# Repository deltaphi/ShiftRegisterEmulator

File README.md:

# ShiftRegisterEmulator
An emulator for a 16-bit shift register. The behavior of this Sketch mimicks
the behavior of an S88 module (i.e., a chain of two 4014B Chips).
The Sketch is set up so that the Arduinos can be Daisy-Chained.

## Hardware Notes

The sketch does not use serial (almost all IO pins are needed). It is set up
not to use the Oscillator Pins. The Sketch can thus be used both with an
external oscillator (e.g., Arduino Board) or without (e.g., Breadboard Setup).

Attempts have been made for a minimal parts setup, where the internal pullup
resistors are used. Thus, you would need only the Atmega and a pull-up resistor
for the reset pin. Unfortunately, I have had repeated trouble with the internal
pull-ups not working as expected (e.g., pulling *down* instead or being an
apparent short), so the default setup is to use external pullups.

In a 3.3V setting, the sketch works when you wire the Atmega up as follows:
* XTAL pins are left open
* All other pins are pulled high using 10k or 47k. Note that the DATA_OUT pin
  does not actually need a pull-up, but having one doesn't hurt functionality.

Note that you can conveniently use star-shaped resistor networks to pull all
pins high with only a few parts.

Note that I have not calculated the input current requirements on the shift
register pins. I use a 74HC367 current driver wired to an ESP32 to drive
the shift register.

### S88 Notes

Here is a not if you want to use this sketch to simulate an S88 module for your
model railroad. This sketch implements the latches of the 4044B chips on an S88
module in software. Therefore, it uses fewer lines. In S88 there are two lines
used for loading the register: "LOAD"/"PS" and "RESET". This sketch only uses
the "LOAD"/"PS" line.

At least on a 16 MHz Arduino, this sketch worked with the most agressive S88
timing I could find (~50us clock). Tests on an 8 MHz Arduino have not been
perfomed yet.

## Software Notes

This sketch was written with [PlatformIO](https://platformio.org/) using the
Arduino framework. It should easily be possible to build and upload it using
the Arduino IDE. You need to rename [src/main.cpp] to something with a
```.ino``` file extension and install the digitalWriteFast library in your
Arduino IDE (not available through the library manager, sadly).

## Why emulate a shift register?

This project started because I needed a bunch of shift register inputs and had
lots of Atmega168 but no 4041B lying around.

## Upcoming Features

* Correct reception of 16 input bits
* Debouncing of input pins over multiple reset-cycles
* Figure out whether using the internal pullups is a good idea (might overload
  the Atmegas' current capacity).

# Dependencies

This sketch uses the digitalWriteFast library (see git submodules).

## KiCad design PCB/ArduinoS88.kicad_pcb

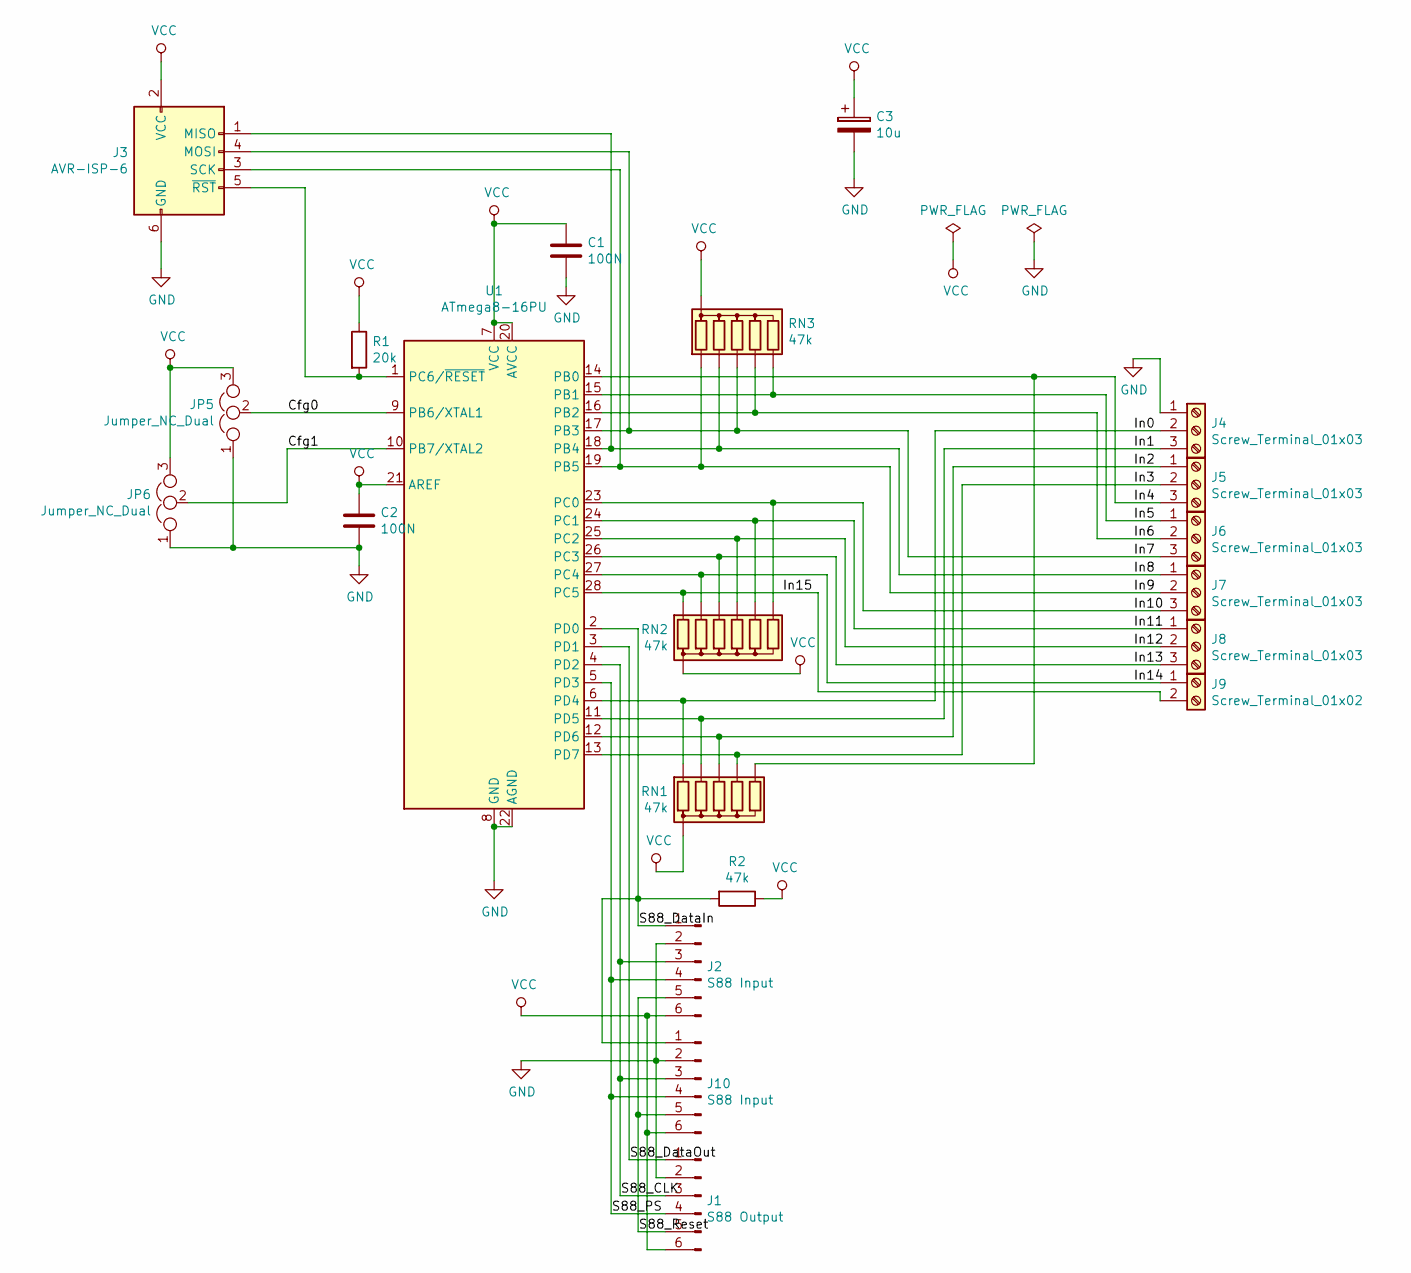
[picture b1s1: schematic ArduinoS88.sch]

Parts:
C1, C2: 100N; C_Disc_D3.0mm_W1.6mm_P2.50mm
C3: 10u; CP_Radial_D4.0mm_P1.50mm
J1: S88 Output; PinHeader_1x06_P2.54mm_Horizontal
J2: S88 Input; PinSocket_1x06_P2.54mm_Horizontal
J3: AVR-ISP-6; IDC-Header_2x03_P2.54mm_Vertical
J4, J5, J6, J7, J8: Screw_Terminal_01x03; TerminalBlock_bornier-3_P5.08mm
J9: Screw_Terminal_01x02; TerminalBlock_bornier-2_P5.08mm
J10: S88 Input; Molex_KK-254_AE-6410-06A_1x06_P2.54mm_Vertical
JP5, JP6: Jumper_NC_Dual; PinHeader_1x03_P2.54mm_Vertical
R1: 20k; R_Axial_DIN0207_L6.3mm_D2.5mm_P10.16mm_Horizontal
R2: 47k; R_Axial_DIN0207_L6.3mm_D2.5mm_P10.16mm_Horizontal
RN1, RN3: 47k; R_Array_SIP6
RN2: 47k; R_Array_SIP7
U1: ATmega8-16PU; DIP-28_W7.62mm

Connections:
/Cfg0: JP5.2, U1.9 (PB6/XTAL1)
/Cfg1: JP6.2, U1.10 (PB7/XTAL2)
/In0: J4.2, RN1.2 (R1), U1.6 (PD4)
/In1: J4.3, RN1.3 (R2), U1.11 (PD5)
/In2: J5.1, RN1.4 (R3), U1.12 (PD6)
/In3: J5.2, RN1.5 (R4), U1.13 (PD7)
/In4: J5.3, RN1.6 (R5), U1.14 (PB0)
/In5: J6.1, RN3.6 (R5), U1.15 (PB1)
/In6: J6.2, RN3.5 (R4), U1.16 (PB2)
/In7: J3.4 (MOSI), J6.3, RN3.4 (R3), U1.17 (PB3)
/In8: J3.1 (MISO), J7.1, RN3.3 (R2), U1.18 (PB4)
/In9: J3.3 (SCK), J7.2, RN3.2 (R1), U1.19 (PB5)
/In10: J7.3, RN2.7 (R6), U1.23 (PC0)
/In11: J8.1, RN2.6 (R5), U1.24 (PC1)
/In12: J8.2, RN2.5 (R4), U1.25 (PC2)
/In13: J8.3, RN2.4 (R3), U1.26 (PC3)
/In14: J9.1, RN2.3 (R2), U1.27 (PC4)
/In15: J9.2, RN2.2 (R1), U1.28 (PC5)
/S88_CLK: J1.3, J2.3, J10.3, U1.4 (PD2)
/S88_DataIn: J2.1, J10.1, R2.2, U1.2 (PD0)
/S88_DataOut: J1.1, U1.3 (PD1)
/S88_PS: J1.4, J2.4, J10.4, U1.5 (PD3)
/S88_Reset: J1.5, J2.5, J10.5
GND: C1.2, C2.2, C3.2, J1.2, J2.2, J3.6 (GND), J4.1, J10.2, JP5.1, JP6.1, U1.8 (GND), U1.22 (AGND)
unnamed: J3.5 (~RST), R1.2, U1.1 (PC6/~RESET)
VCC: C1.1, C2.1, C3.1, J1.6, J2.6, J3.2 (VCC), J10.6, JP5.3, JP6.3, R1.1, R2.1, RN1.1 (common), RN2.1 (common), RN3.1 (common), U1.7 (VCC), U1.20 (AVCC), U1.21 (AREF)

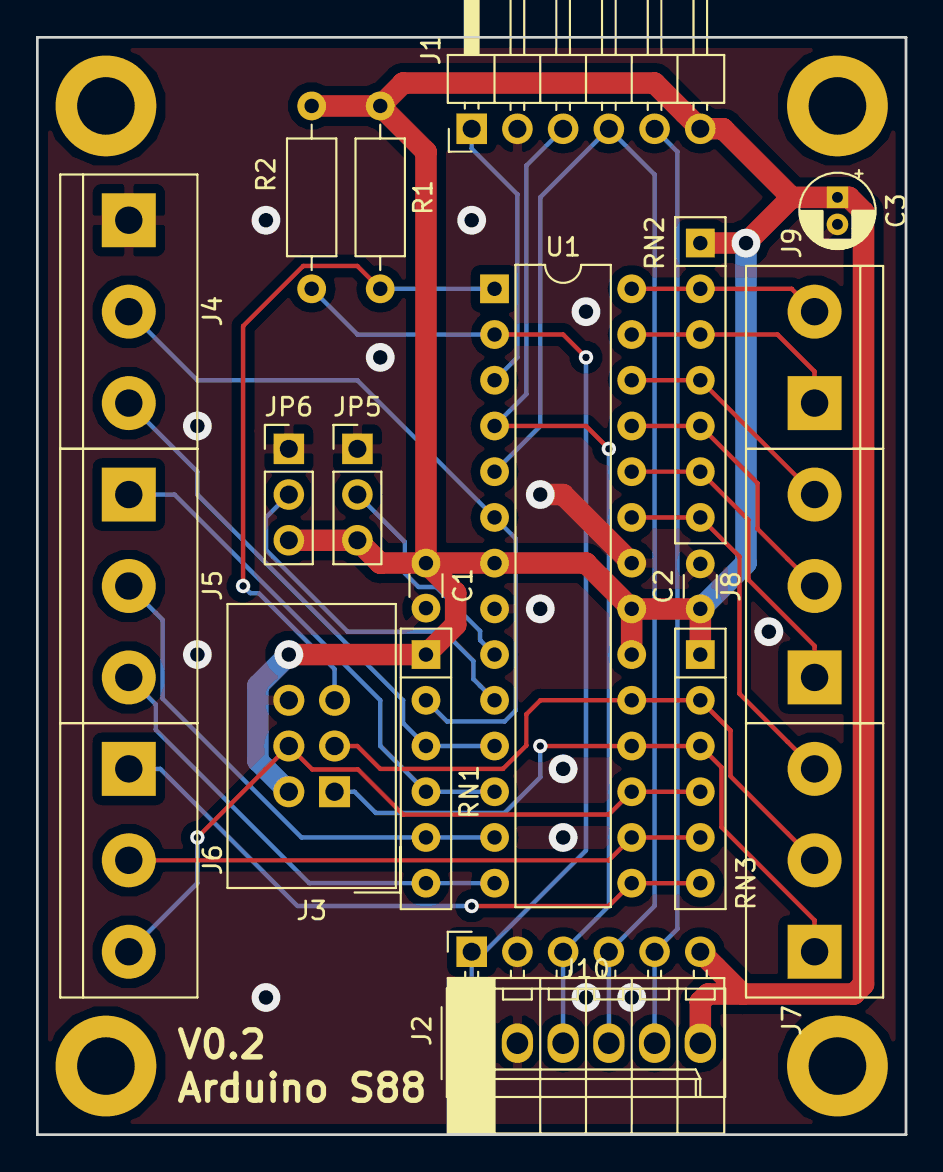
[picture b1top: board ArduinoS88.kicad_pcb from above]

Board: 2 copper layers, 48.3 x 61.0 mm, 21 parts (0 on the bottom side), 26 nets.

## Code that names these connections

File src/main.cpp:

#include <Arduino.h>

#include <digitalWriteFast/digitalWriteFast.h>

// Defines for the shift register pins.
// CLOCK_IN and PS_IN must be interrupt pins
#define CLOCK_IN_PIN (2)
#define PS_IN_PIN (3)
#define DATA_OUT_PIN (1)
#define DATA_IN_PIN (0)

#define PARALLEL_INPUT_PIN_MODE (INPUT)

// The variable holding the actual bits that were read
using RegisterType = uint16_t;
constexpr RegisterType kHighBitMask = 0x8000; // Pattern where the highest bit of RegisterType is set
constexpr RegisterType kLowBitMask = 1U; // Pattern where the lowest bit of RegisterType is set
volatile RegisterType bits;

// Counters for debouncing the inputs
using CounterValueType = uint8_t; // Value-type for the counters
using CountersIndexType = uint8_t; // Type for the index of counters
constexpr CountersIndexType kNumCounters = sizeof(bits)*8;
volatile CounterValueType counters[kNumCounters];

void ClockISR() {
  uint8_t clockValue = digitalReadFast(CLOCK_IN_PIN);
  if (clockValue == HIGH) {
    // Rising edge. Write a new value to the output and shift the register
    digitalWriteFast(DATA_OUT_PIN, bits & kLowBitMask);
    bits >>= 1;
  } else {
    // Falling edge. Sample the input register.
    if (digitalReadFast(DATA_IN_PIN) == HIGH) {
      bits |= kHighBitMask;
    } // else {
      // bit was already zeroed by the shift operation
    // }
  }
}

void PSISR() {
  // Re-Read the bits
  
  // We use them as follows:
  // 15                  10  9                   4   3           0 
  // PC5 PC4 PC3 PC2 PC1 PC0 PB5 PB4 PB3 PB2 PB1 PB0 PD7 PD6 PD5 PD4
  // Thus, start with the lowest input bit at Digital 4 and go counter-clockwise
  // around the chip until you hit input 15 at pin A5.

  bits = ((uint16_t)PINC) << 10; // no mask needed, unused bits are shifted out
  bits |= ((uint16_t)(PINB & 0x3F)) << 4;
  bits |= PIND >> 4; // no mask needed, unused bits are shifted out
  digitalWriteFast(DATA_OUT_PIN, bits & kLowBitMask);
}

void setup() {
  // Reset all states
  bits = 0;
  for (CountersIndexType i = 0; i < kNumCounters; ++i) {
    counters[i] = 0;
  }

  // Configure the data pins. Set all remaining IO pins to input
  pinModeFast(4, PARALLEL_INPUT_PIN_MODE);
  pinModeFast(5, PARALLEL_INPUT_PIN_MODE);
  pinModeFast(6, PARALLEL_INPUT_PIN_MODE);
  pinModeFast(7, PARALLEL_INPUT_PIN_MODE);
  pinModeFast(8, PARALLEL_INPUT_PIN_MODE);
  pinModeFast(9, PARALLEL_INPUT_PIN_MODE);
  pinModeFast(10, PARALLEL_INPUT_PIN_MODE);
  pinModeFast(11, PARALLEL_INPUT_PIN_MODE);
  pinModeFast(12, PARALLEL_INPUT_PIN_MODE);
  pinModeFast(13, PARALLEL_INPUT_PIN_MODE);

  pinModeFast(A0, PARALLEL_INPUT_PIN_MODE);
  pinModeFast(A1, PARALLEL_INPUT_PIN_MODE);
  pinModeFast(A2, PARALLEL_INPUT_PIN_MODE);
  pinModeFast(A3, PARALLEL_INPUT_PIN_MODE);
  pinModeFast(A4, PARALLEL_INPUT_PIN_MODE);
  pinModeFast(A5, PARALLEL_INPUT_PIN_MODE);

  // Configure the Interrupt and Data registers
  pinModeFast(CLOCK_IN_PIN, INPUT);
  pinModeFast(PS_IN_PIN, INPUT);
  pinModeFast(DATA_OUT_PIN, OUTPUT);
  pinModeFast(DATA_IN_PIN, INPUT);
  
  digitalWriteFast(DATA_OUT_PIN, LOW);

  attachInterrupt(digitalPinToInterrupt(CLOCK_IN_PIN), ClockISR, CHANGE);
  attachInterrupt(digitalPinToInterrupt(PS_IN_PIN), PSISR, RISING);
}


void loop() {
  // put your main code here, to run repeatedly:
}

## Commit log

2018-12-23 Initial Import of PlatformIO example
2018-12-23 Initial version. Bug: Output of first bit is duplicated.
2018-12-23 Cleanup
2018-12-23 Update LICENSE
2018-12-23 Further updates to README
2018-12-23 Added notes on PlatformIO and Arduino
2018-12-23 Change Pin Layout to be less dependent on the Board used for testing
2018-12-26 Configured for external pullup
2018-12-29 Support for additional Atmegas
2019-01-02 Iniital commit of the Arduino S88 PCB
2019-01-02 Updated connectors and added Gerber files
2019-01-02 Updated for manufacturing
2019-11-16 Fix an unconnected trace. Bump PCB Version to v0.2.
2020-06-08 Added Github Workflow
2020-06-08 Added status badge
